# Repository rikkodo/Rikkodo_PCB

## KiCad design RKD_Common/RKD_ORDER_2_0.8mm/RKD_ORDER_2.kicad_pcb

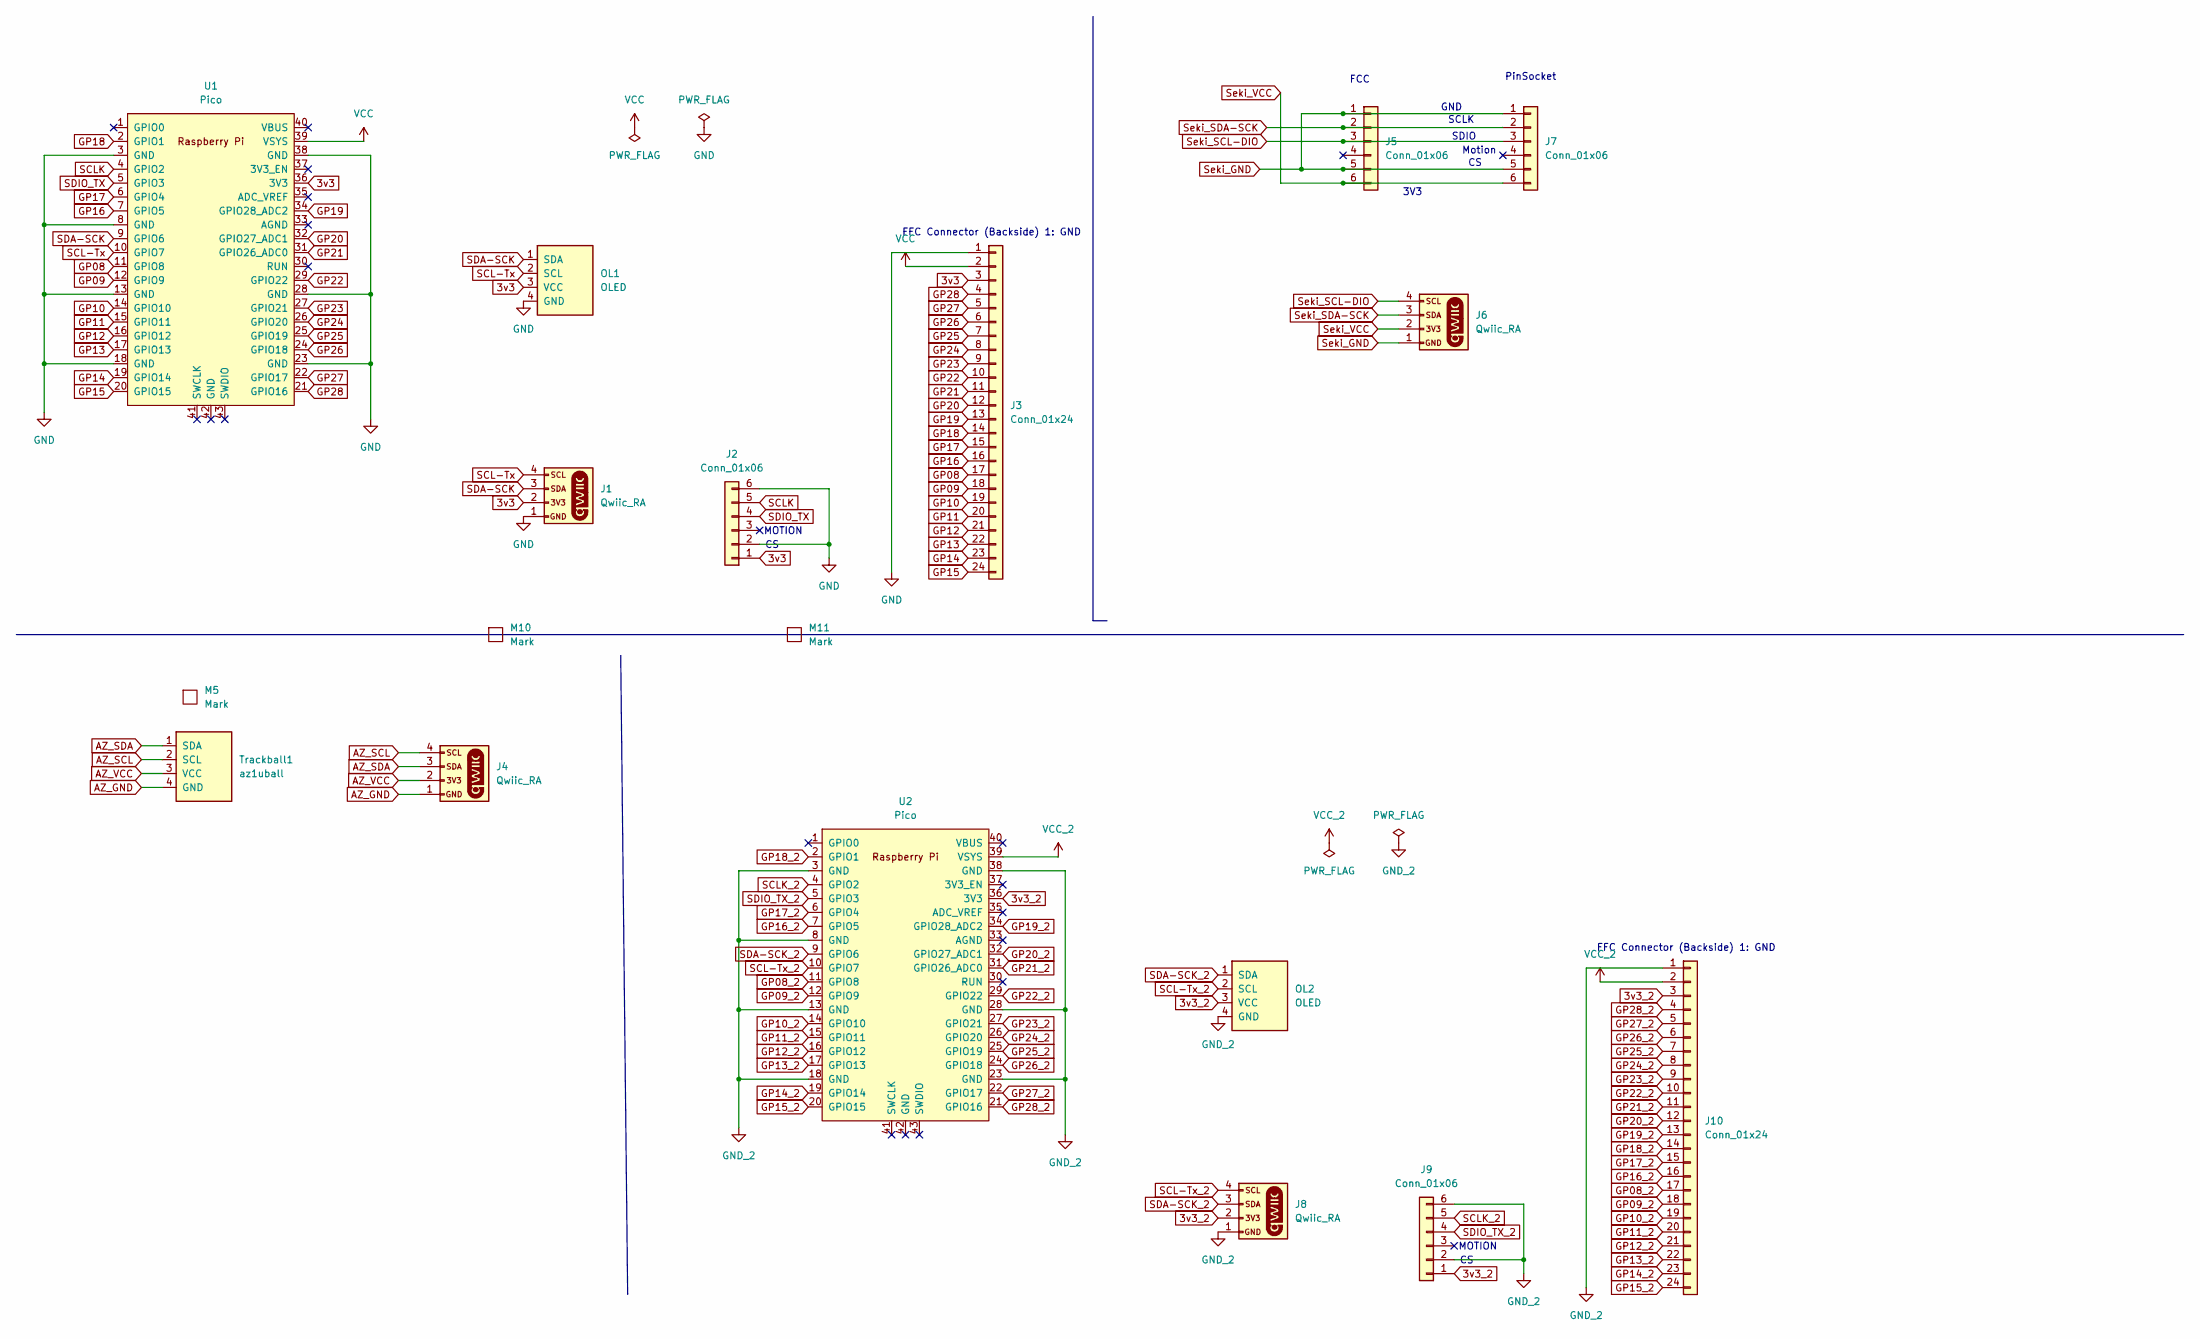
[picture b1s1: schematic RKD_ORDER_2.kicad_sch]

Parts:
J1, J4, J6, J8: Qwiic_RA; JST_SMD_1.0mm-4_Black
J2, J5, J9: Conn_01x06; Hirose_FH12-6S-0.5SH_1x06-1MP_P0.50mm_Horizontal
J3, J10: Conn_01x24; Hirose_FH12-24S-0.5SH_1x24-1MP_P0.50mm_Horizontal
J7: Conn_01x06; PinHeader_1x06_P2.54mm_Vertical
M5: Mark; rkd_Point_Screw_Hall
M10, M11: Mark; rkd_cutdot
OL1, OL2: OLED; OLED_center_display
Trackball1: az1uball; AZ1UBALL
U1, U2: Pico; rkd_RPi_Pico_TH_NODBG

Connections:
3v3: J1.2, J2.1, J3.3, OL1.3 (VCC), U1.36 (3V3)
3v3_2: J8.2, J9.1, J10.3, OL2.3 (VCC), U2.36 (3V3)
AZ_GND: J4.1, Trackball1.4 (GND)
AZ_SCL: J4.4, Trackball1.2 (SCL)
AZ_SDA: J4.3, Trackball1.1 (SDA)
AZ_VCC: J4.2, Trackball1.3 (VCC)
GND: J1.1, J2.2, J2.6, J3.1, OL1.4 (GND), U1.3 (GND), U1.8 (GND), U1.13 (GND), U1.18 (GND), U1.23 (GND), U1.28 (GND), U1.38 (GND)
GND_2: J8.1, J9.2, J9.6, J10.1, OL2.4 (GND), U2.3 (GND), U2.8 (GND), U2.13 (GND), U2.18 (GND), U2.23 (GND), U2.28 (GND), U2.38 (GND)
GP08: J3.17, U1.11 (GPIO8)
GP08_2: J10.17, U2.11 (GPIO8)
GP09: J3.18, U1.12 (GPIO9)
GP09_2: J10.18, U2.12 (GPIO9)
GP10: J3.19, U1.14 (GPIO10)
GP10_2: J10.19, U2.14 (GPIO10)
GP11: J3.20, U1.15 (GPIO11)
GP11_2: J10.20, U2.15 (GPIO11)
GP12: J3.21, U1.16 (GPIO12)
GP12_2: J10.21, U2.16 (GPIO12)
GP13: J3.22, U1.17 (GPIO13)
GP13_2: J10.22, U2.17 (GPIO13)
GP14: J3.23, U1.19 (GPIO14)
GP14_2: J10.23, U2.19 (GPIO14)
GP15: J3.24, U1.20 (GPIO15)
GP15_2: J10.24, U2.20 (GPIO15)
GP16: J3.16, U1.7 (GPIO5)
GP16_2: J10.16, U2.7 (GPIO5)
GP17: J3.15, U1.6 (GPIO4)
GP17_2: J10.15, U2.6 (GPIO4)
GP18: J3.14, U1.2 (GPIO1)
GP18_2: J10.14, U2.2 (GPIO1)
GP19: J3.13, U1.34 (GPIO28_ADC2)
GP19_2: J10.13, U2.34 (GPIO28_ADC2)
GP20: J3.12, U1.32 (GPIO27_ADC1)
GP20_2: J10.12, U2.32 (GPIO27_ADC1)
GP21: J3.11, U1.31 (GPIO26_ADC0)
GP21_2: J10.11, U2.31 (GPIO26_ADC0)
GP22: J3.10, U1.29 (GPIO22)
GP22_2: J10.10, U2.29 (GPIO22)
GP23: J3.9, U1.27 (GPIO21)
GP23_2: J10.9, U2.27 (GPIO21)
GP24: J3.8, U1.26 (GPIO20)
GP24_2: J10.8, U2.26 (GPIO20)
GP25: J3.7, U1.25 (GPIO19)
GP25_2: J10.7, U2.25 (GPIO19)
GP26: J3.6, U1.24 (GPIO18)
GP26_2: J10.6, U2.24 (GPIO18)
GP27: J3.5, U1.22 (GPIO17)
GP27_2: J10.5, U2.22 (GPIO17)
GP28: J3.4, U1.21 (GPIO16)
GP28_2: J10.4, U2.21 (GPIO16)
SCL-Tx: J1.4, OL1.2 (SCL), U1.10 (GPIO7)
SCL-Tx_2: J8.4, OL2.2 (SCL), U2.10 (GPIO7)
SCLK: J2.5, U1.4 (GPIO2)
SCLK_2: J9.5, U2.4 (GPIO2)
SDA-SCK: J1.3, OL1.1 (SDA), U1.9 (GPIO6)
SDA-SCK_2: J8.3, OL2.1 (SDA), U2.9 (GPIO6)
SDIO_TX: J2.4, U1.5 (GPIO3)
SDIO_TX_2: J9.4, U2.5 (GPIO3)
Seki_GND: J5.1, J5.5, J6.1, J7.1, J7.5
Seki_SCL-DIO: J5.3, J6.4, J7.3
Seki_SDA-SCK: J5.2, J6.3, J7.2
Seki_VCC: J5.6, J6.2, J7.6
VCC: J3.2, U1.39 (VSYS)
VCC_2: J10.2, U2.39 (VSYS)

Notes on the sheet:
FCC
PinSocket
3V3
SCLK
FFC Connector (Backside) 1: GND
MOTION
Motion
SDIO
GND

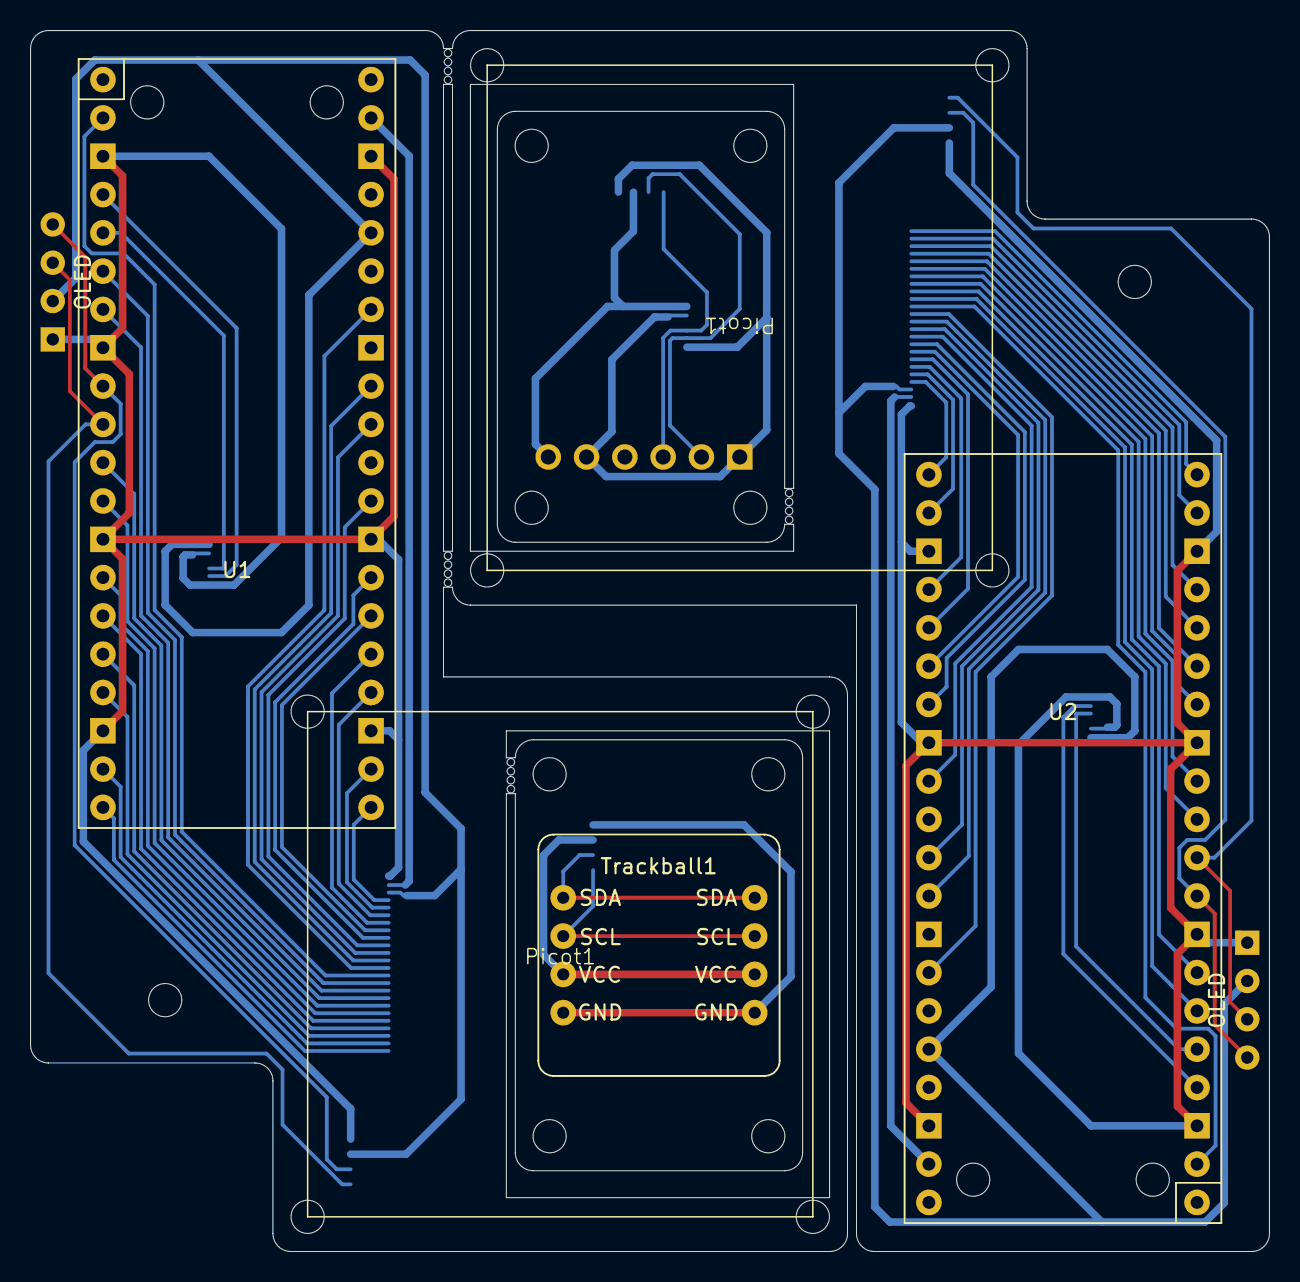
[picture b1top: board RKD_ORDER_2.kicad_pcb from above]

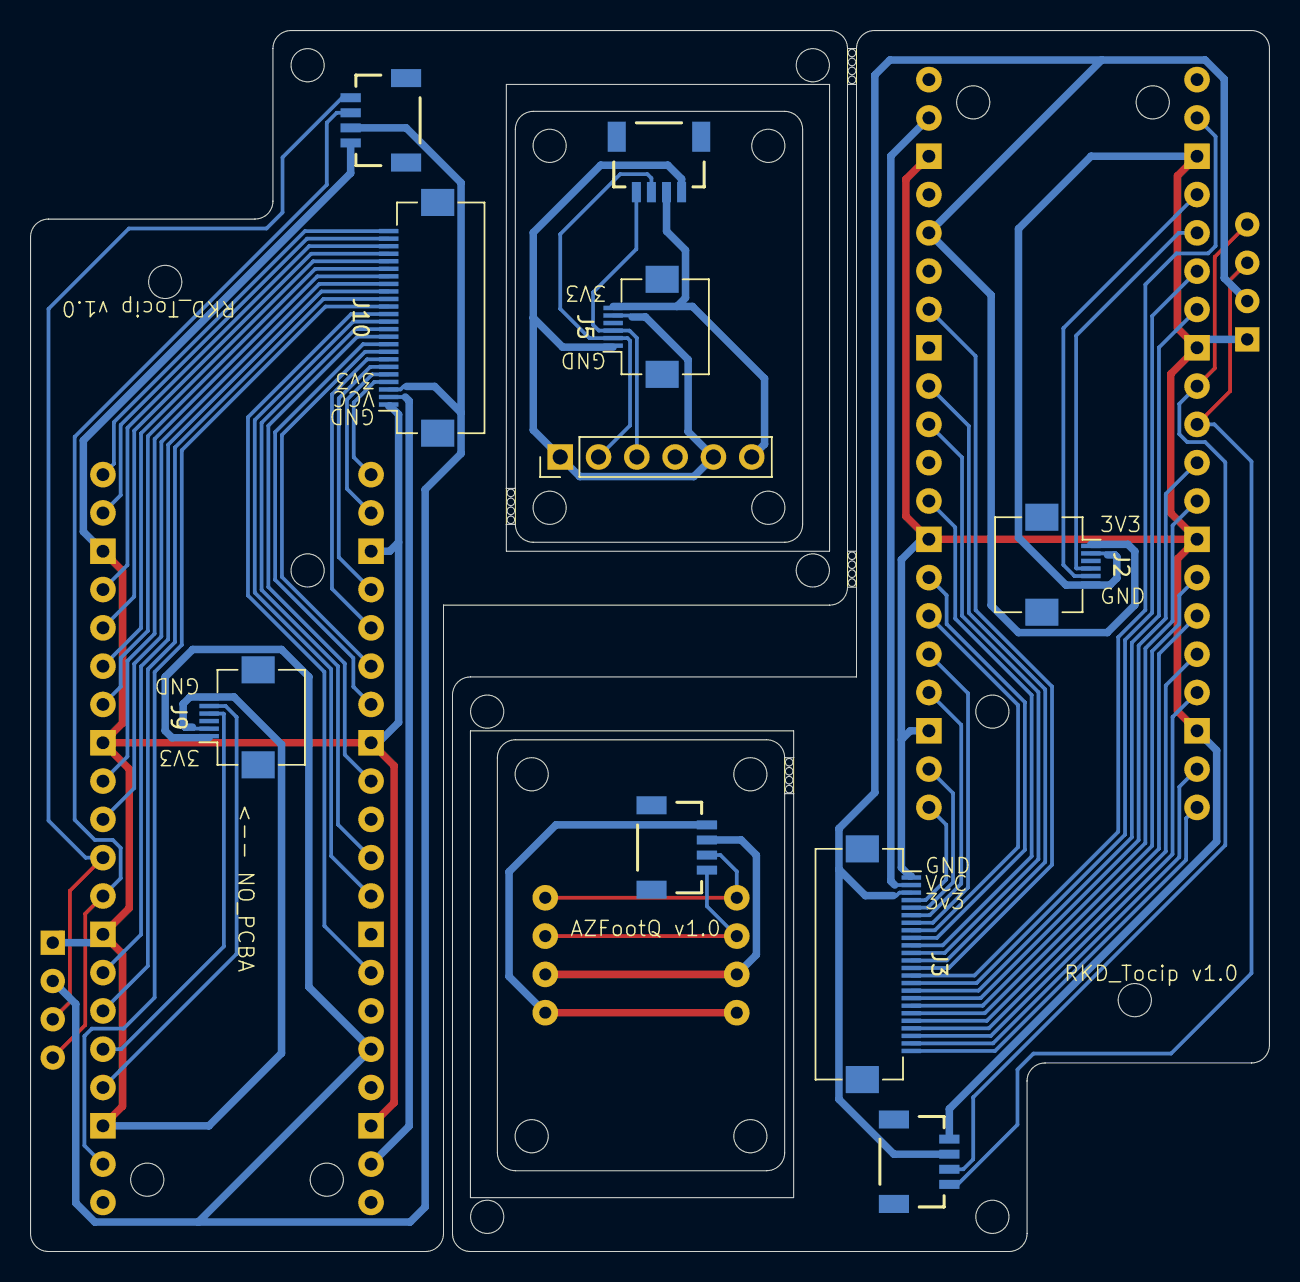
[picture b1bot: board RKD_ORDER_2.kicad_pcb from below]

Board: 2 copper layers, 82.2 x 81.0 mm, 31 parts (10 on the bottom side), 64 nets.

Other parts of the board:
M2, M2#2, M3, M3#2, M9, M9#2: Mark; m2_Screw_Hole
M6: Mark; rkd_Point_Screw_Hall
M7, M8: rkd_SekiBall_ScrewHall
M10#2, M10#3: Mark; rkd_cutdot
Picot1, Picot1#2: rkd_picot5400_BTM

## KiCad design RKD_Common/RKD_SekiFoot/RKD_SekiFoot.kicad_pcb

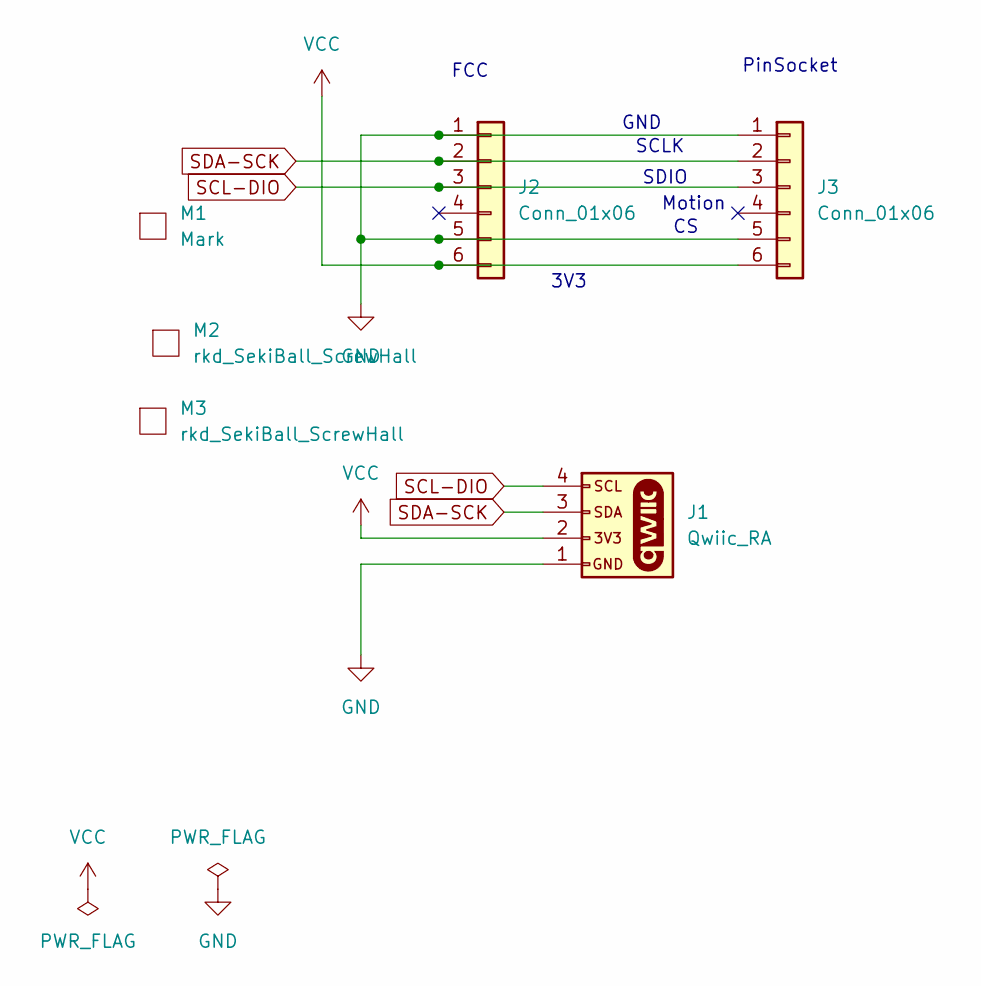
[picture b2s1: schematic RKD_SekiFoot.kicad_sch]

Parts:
J1: Qwiic_RA; JST_SMD_1.0mm-4_Black
J2: Conn_01x06; Hirose_FH12-6S-0.5SH_1x06-1MP_P0.50mm_Horizontal
J3: Conn_01x06; PinHeader_1x06_P2.54mm_Vertical
M1: Mark; rkd_Point_Cut
M2, M3: rkd_SekiBall_ScrewHall

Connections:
GND: J1.1, J2.1, J2.5, J3.1, J3.5
SCL-DIO: J1.4, J2.3, J3.3
SDA-SCK: J1.3, J2.2, J3.2
VCC: J1.2, J2.6, J3.6

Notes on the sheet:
3V3
FCC
PinSocket
SDIO
SCLK
GND
Motion

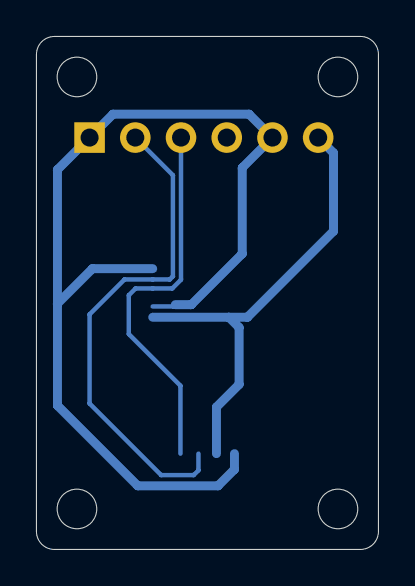
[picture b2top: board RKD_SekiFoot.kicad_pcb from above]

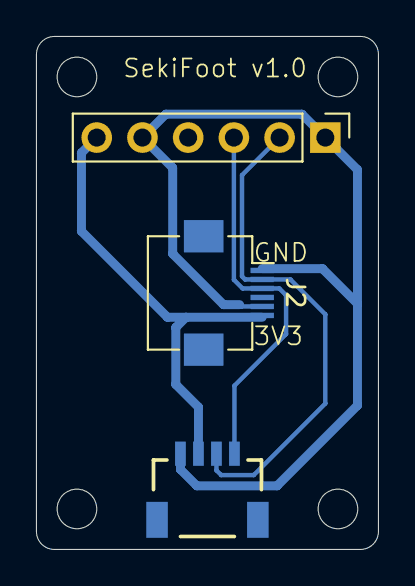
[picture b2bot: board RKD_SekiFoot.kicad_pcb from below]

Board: 2 copper layers, 19.0 x 28.5 mm, 6 parts (3 on the bottom side), 4 nets.

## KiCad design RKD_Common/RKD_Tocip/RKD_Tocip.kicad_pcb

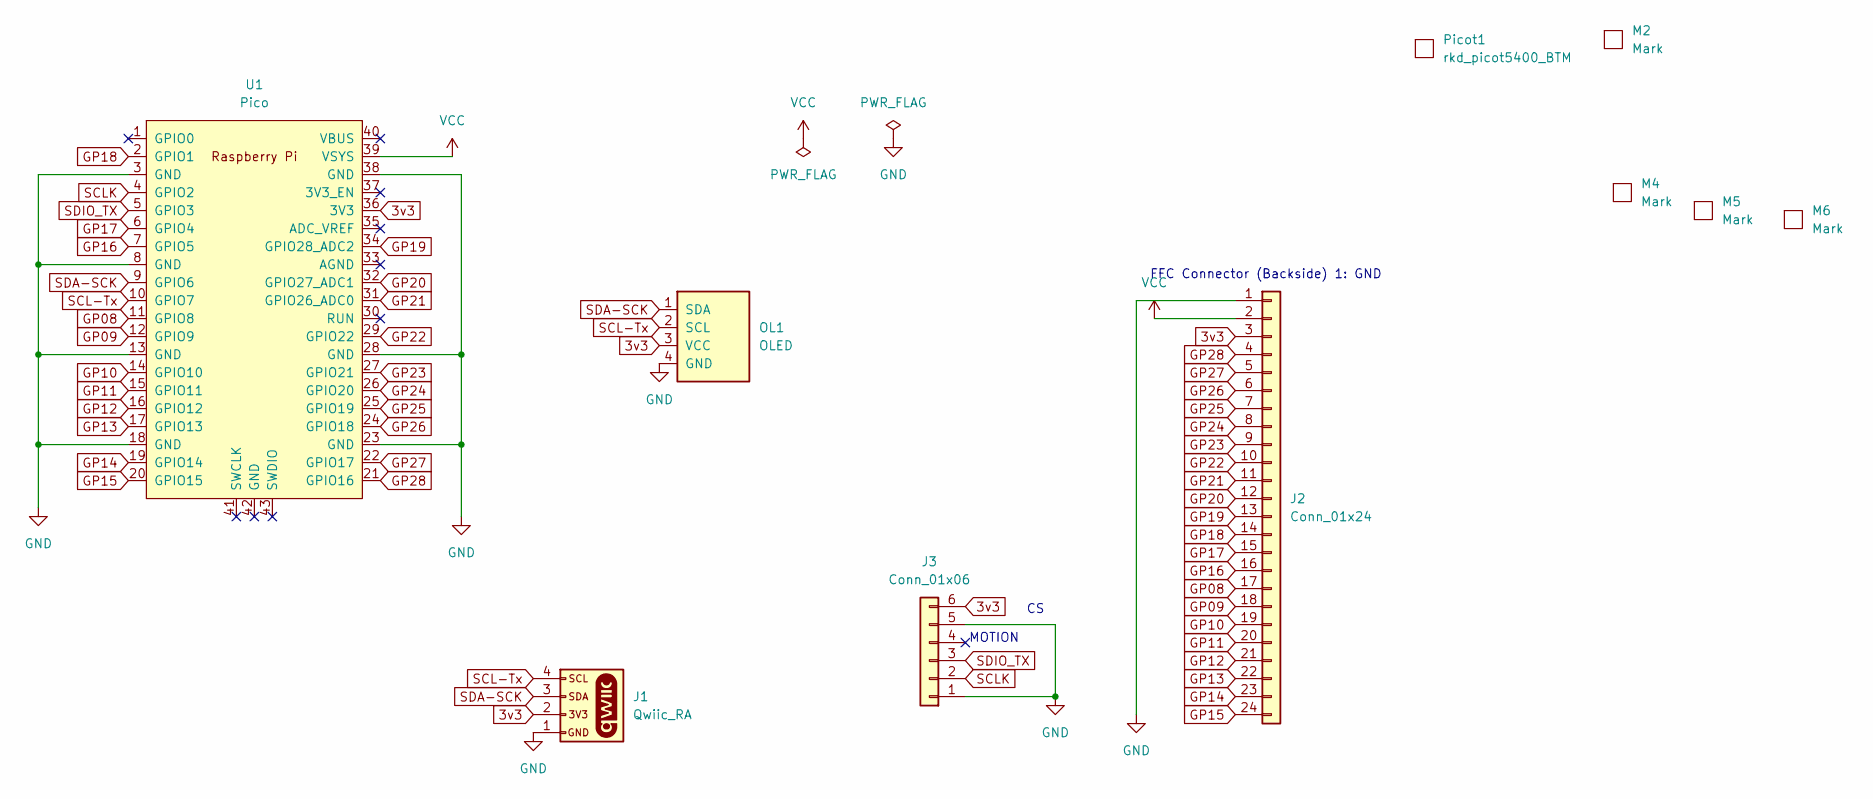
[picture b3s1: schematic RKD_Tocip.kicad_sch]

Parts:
J1: Qwiic_RA; JST_SMD_1.0mm-4_Black
J2: Conn_01x24; Hirose_FH12-24S-0.5SH_1x24-1MP_P0.50mm_Horizontal
J3: Conn_01x06; Hirose_FH12-6S-0.5SH_1x06-1MP_P0.50mm_Horizontal
M2: Mark; rkd_Point_Hall
M4, M5, M6: Mark; m2_Screw_Hole
OL1: OLED; OLED_center_display
Picot1: rkd_picot5400_BTM
U1: Pico; rkd_RPi_Pico_TH_NODBG

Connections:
3v3: J1.2, J2.3, J3.6, OL1.3 (VCC), U1.36 (3V3)
GND: J1.1, J2.1, J3.1, J3.5, OL1.4 (GND), U1.3 (GND), U1.8 (GND), U1.13 (GND), U1.18 (GND), U1.23 (GND), U1.28 (GND), U1.38 (GND)
GP08: J2.17, U1.11 (GPIO8)
GP09: J2.18, U1.12 (GPIO9)
GP10: J2.19, U1.14 (GPIO10)
GP11: J2.20, U1.15 (GPIO11)
GP12: J2.21, U1.16 (GPIO12)
GP13: J2.22, U1.17 (GPIO13)
GP14: J2.23, U1.19 (GPIO14)
GP15: J2.24, U1.20 (GPIO15)
GP16: J2.16, U1.7 (GPIO5)
GP17: J2.15, U1.6 (GPIO4)
GP18: J2.14, U1.2 (GPIO1)
GP19: J2.13, U1.34 (GPIO28_ADC2)
GP20: J2.12, U1.32 (GPIO27_ADC1)
GP21: J2.11, U1.31 (GPIO26_ADC0)
GP22: J2.10, U1.29 (GPIO22)
GP23: J2.9, U1.27 (GPIO21)
GP24: J2.8, U1.26 (GPIO20)
GP25: J2.7, U1.25 (GPIO19)
GP26: J2.6, U1.24 (GPIO18)
GP27: J2.5, U1.22 (GPIO17)
GP28: J2.4, U1.21 (GPIO16)
SCL-Tx: J1.4, OL1.2 (SCL), U1.10 (GPIO7)
SCLK: J3.2, U1.4 (GPIO2)
SDA-SCK: J1.3, OL1.1 (SDA), U1.9 (GPIO6)
SDIO_TX: J3.3, U1.5 (GPIO3)
VCC: J2.2, U1.39 (VSYS)

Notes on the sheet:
MOTION
FFC Connector (Backside) 1: GND

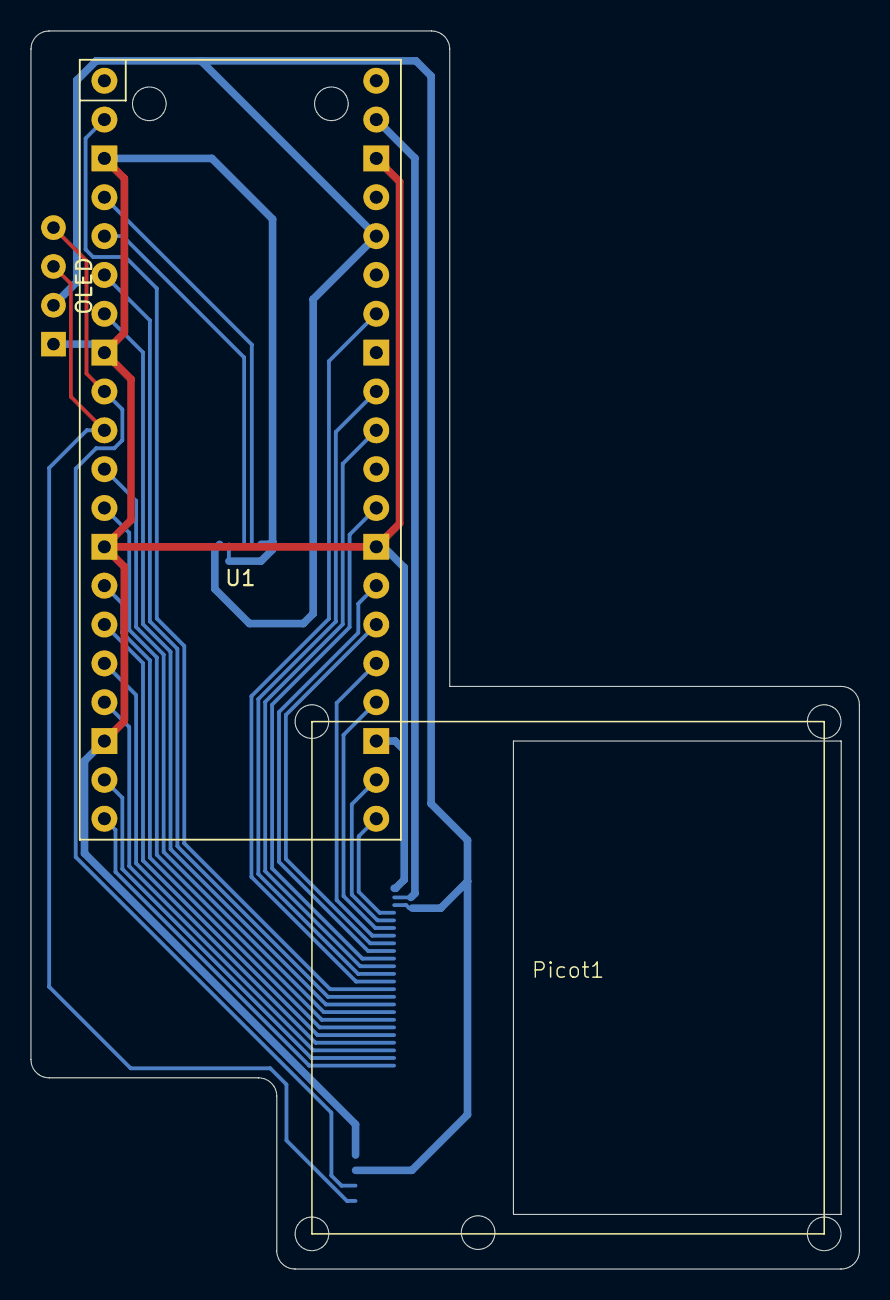
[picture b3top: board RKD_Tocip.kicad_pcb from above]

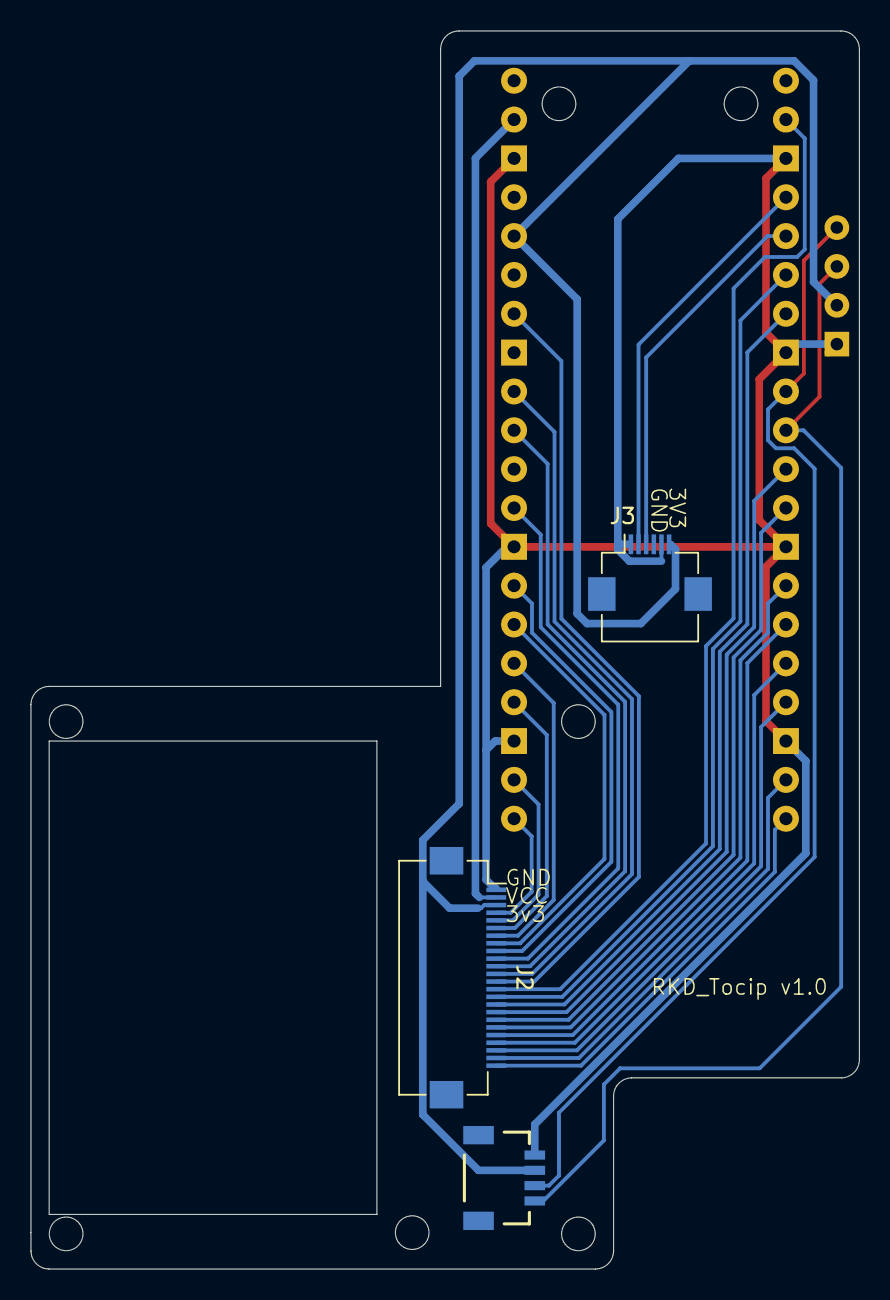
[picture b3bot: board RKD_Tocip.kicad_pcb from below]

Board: 2 copper layers, 54.2 x 81.0 mm, 10 parts (3 on the bottom side), 28 nets.
